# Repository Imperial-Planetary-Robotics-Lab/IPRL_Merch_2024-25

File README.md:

# IPRL_Merch_2024-25
 All the files for the merch

IPRL Rulers:\
[2024 Edition](https://github.com/Imperial-Planetary-Robotics-Lab/IPRL_Merch_2024-25/tree/main/IPRL_2024_Ruler)

[2025 Edition](https://github.com/Imperial-Planetary-Robotics-Lab/IPRL_Merch_2024-25/tree/main/IPRL_2025_Ruler)

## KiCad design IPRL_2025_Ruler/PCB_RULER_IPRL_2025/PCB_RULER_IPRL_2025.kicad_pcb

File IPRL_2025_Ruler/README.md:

# ICRS PCB Ruler

A 15cm PCB ruler variant designed for IPRL. Forked from [here](https://github.com/ben5049/ICRS-PCB-Ruler) (with consent!) It can be easily adapted/rebranded using the KiCad project in this repository.

Front:

Back:

## KiCad Project
To open this project in KiCad 9.0 clone this repository and open the .kicad_pro file in [Ruler_KiCad](Ruler_KiCad). Next open the PCB editor and go to `Preferences > Manage Footprint Libraries > Add Existing` (the folder icon below the list of libraries). Then navigate to `Ruler_KiCad/ruler_footprints` and click "select folder". This is in order to get the custom footprints used in this project.

## Ordering
### PCB
The gerber files needed for ordering can be found in [Ruler_gerbers.zip](https://github.com/Imperial-Planetary-Robotics-Lab/IPRL_Merch_2024-25/blob/main/IPRL_2025_Ruler/PCB_RULER_IPRL_2025/PCB_RULER_IPRL_2025_GERBER.zip). Simply upload this .zip file to any PCB manufacturer's website.

The recommended specifications for ordering this PCB are as follows:
* 2 Layers
* 1.6mm thick FR4
* White silkscreen
* ENIG surface finish
* <= 1 oz Copper weight
* Tented vias
* +- 0.2mm Board outline tolerance
* Remove order number

### Stencils

The stencils are also recommended to order, make sure that customised size is chosen of 160x30. Everything else should be the default values.

## BoM

For the rest of the components on the ruler, here's the bill of materials, that can be bought in bulk in aliExpress

| Reference  | Qty | Value                         | Datasheet                                                                       |
|------------|-----|-------------------------------|---------------------------------------------------------------------------------|
| C101       | 1   | 470p 0402 Capacitor           | ~                                                                               |
| C102       | 1   | 220n 0402 Capacitor           | ~                                                                               |
| C103       | 1   | 1u 0402 Capacitor             | ~                                                                               |
| D101-D112  | 12  | 0402 SMD LED                  | ~                                                                               |
| IC101      | 1   | NT3H2211W0FTTJ                | http://www.nxp.com/docs/en/data-sheet/NT3H2111_2211.pdf                         |
| J101       | 1   | USB_C_Receptacle_PowerOnly_6P | https://www.usb.org/sites/default/files/documents/usb_type-c.zip                |
| R102       | 1   | 47k 0402 Resistor             | ~                                                                               |
| R101, R103 | 1   | 470  0402 Resistor            | ~                                                                               |
| R104,R105  | 2   | 1k  0402 Resistor             | ~                                                                               |
| U101       | 1   | NE555D Clock                  | http://www.ti.com/lit/ds/symlink/ne555.pdf                                      |
| U102       | 1   | 4017 Decade Counter           | http://www.intersil.com/content/dam/Intersil/documents/cd40/cd4017bms-22bms.pdf |

## Assembly and Setup

For the assembly and setup, here's the step-by-step instruction

1. Put solder paste using the stencil, make sure it's cleaned with IPA to avoid putting the paste somewhere else!
2. Put components on top, ensuring correct polarity for the LEDs and ICs (there's usually a dot or a marker to show that)
3. Make sure there's no short, you can start testing it by plugging in the USB-C. The LED under the usb shows power input. If there's no problem, then the LED should start flicking through the symbols.
4. For the NFC, it's a little bit more complicated. First, one person needs to install the NXP tagwriter app.
5. Select Erase tags -> Erase & format as NDEF -> input 2000 bytes -> scan with phone. If you don't know where the NFC on the phone is, the LED on the NFC IC will light up if you're at the right place.
6. Now you should be able to program it with the NFC tools to your heart's content.

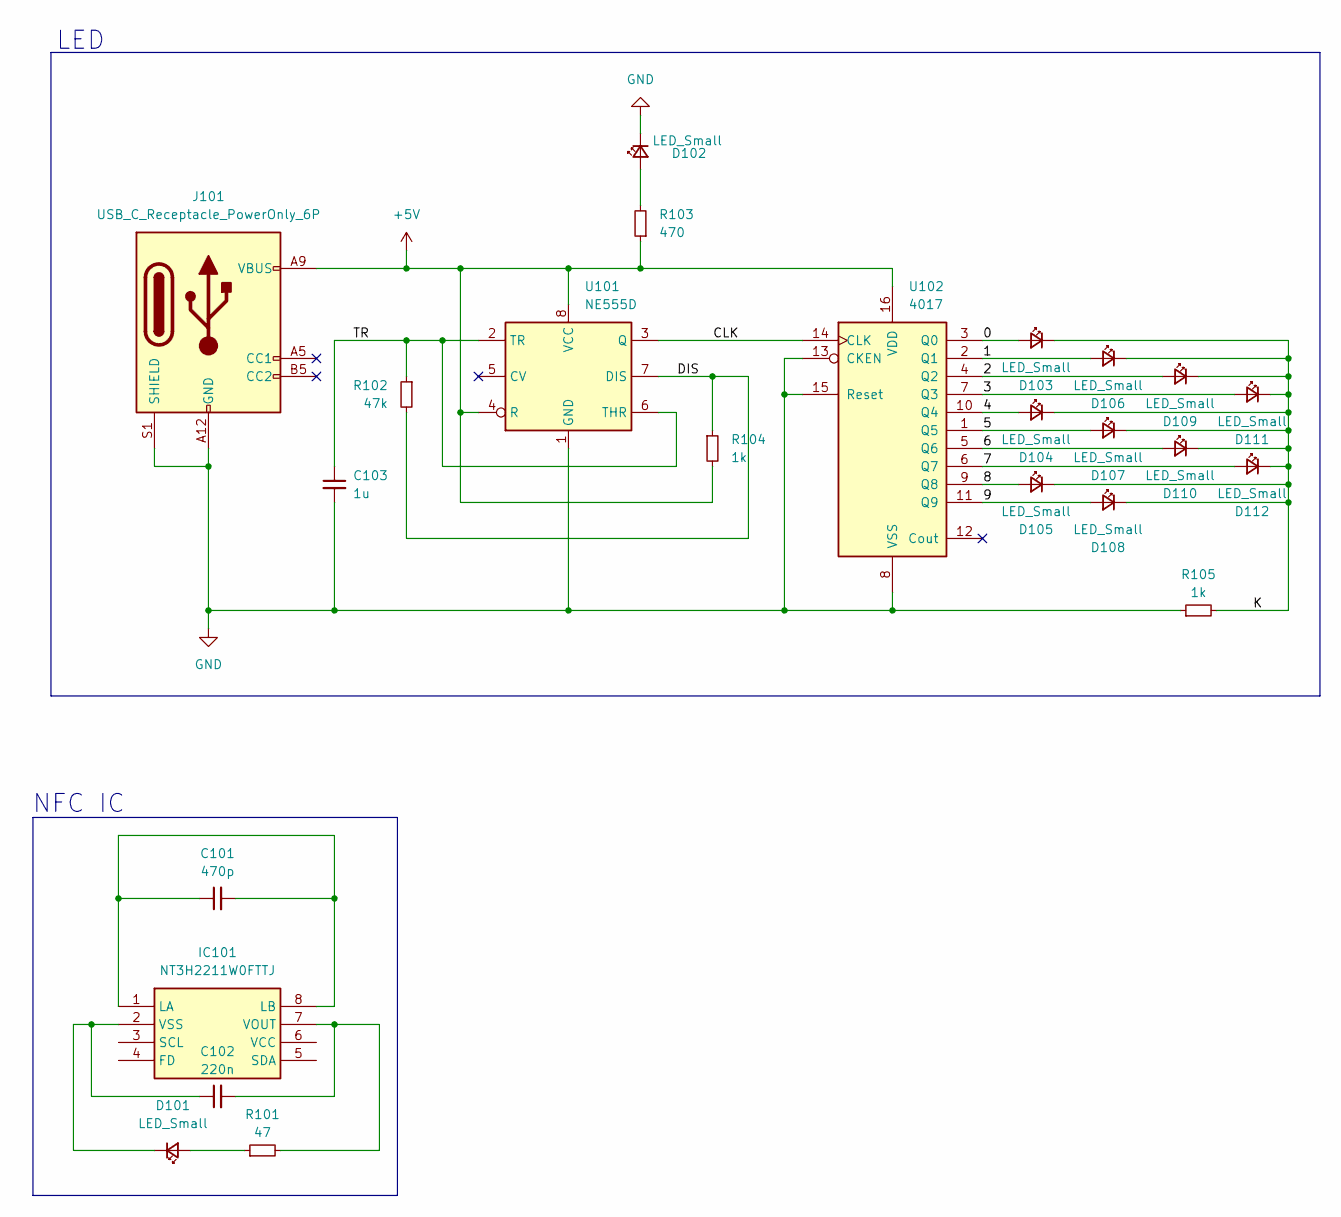
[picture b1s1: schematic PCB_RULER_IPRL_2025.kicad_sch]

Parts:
C101: 470p; C_0402_1005Metric
C102: 220n; C_0402_1005Metric
C103: 1u; C_0402_1005Metric
D101, D102, D103, D104, D105, D106, D107, D108, D109, D110, D111, D112: LED_Small; LED_0402_1005Metric
IC101: NT3H2211W0FTTJ; SOP65P490X110-8N; Mouser Part Number 771-NT3H2211W0FTTJ
J101: USB_C_Receptacle_PowerOnly_6P; USB_C_Receptacle_GCT_USB4135-GF-A_6P_TopMnt_Horizontal
R101: 47; R_0402_1005Metric
R102: 47k; R_0402_1005Metric
R103: 470; R_0402_1005Metric
R104, R105: 1k; R_0402_1005Metric
U101: NE555D; SOIC-8_3.9x4.9mm_P1.27mm
U102: 4017; SOP-16_3.9x9.9mm_P1.27mm

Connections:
+5V: J101.A9 (VBUS), J101.B9 (VBUS), R103.1, R104.2, U101.4 (R), U101.8 (VCC), U102.16 (VDD)
/0: D103.2 (A), U102.3 (Q0)
/1: D106.2 (A), U102.2 (Q1)
/2: D109.2 (A), U102.4 (Q2)
/3: D111.2 (A), U102.7 (Q3)
/4: D104.2 (A), U102.10 (Q4)
/5: D107.2 (A), U102.1 (Q5)
/6: D110.2 (A), U102.5 (Q6)
/7: D112.2 (A), U102.6 (Q7)
/8: D105.2 (A), U102.9 (Q8)
/9: D108.2 (A), U102.11 (Q9)
/CLK: U101.3 (Q), U102.14 (CLK)
/DIS: R102.2, R104.1, U101.7 (DIS)
/K: D103.1 (K), D104.1 (K), D105.1 (K), D106.1 (K), D107.1 (K), D108.1 (K), D109.1 (K), D110.1 (K), D111.1 (K), D112.1 (K), R105.2
/TR: C103.1, R102.1, U101.2 (TR), U101.6 (THR)
GND: C103.2, D102.1 (K), J101.A12 (GND), J101.B12 (GND), J101.S1 (SHIELD), R105.1, U101.1 (GND), U102.8 (VSS), U102.13 (CKEN), U102.15 (Reset)
unnamed: D101.2 (A), R101.1
unnamed: C102.1, D101.1 (K), IC101.2 (VSS)
unnamed: D102.2 (A), R103.2
unnamed: C101.1, C101.2, IC101.1 (LA), IC101.8 (LB)
unnamed: C102.2, IC101.7 (VOUT), R101.2

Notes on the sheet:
LED
NFC IC

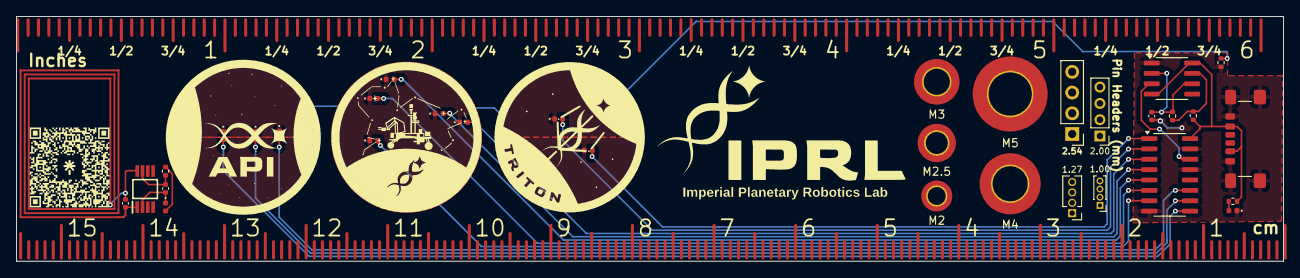
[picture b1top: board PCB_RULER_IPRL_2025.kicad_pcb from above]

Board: 2 copper layers, 155.3 x 30.0 mm, 25 parts (0 on the bottom side), 21 nets.

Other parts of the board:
M2: MountingHole_2.2mm_M2_DIN965_Pad_TopBottom

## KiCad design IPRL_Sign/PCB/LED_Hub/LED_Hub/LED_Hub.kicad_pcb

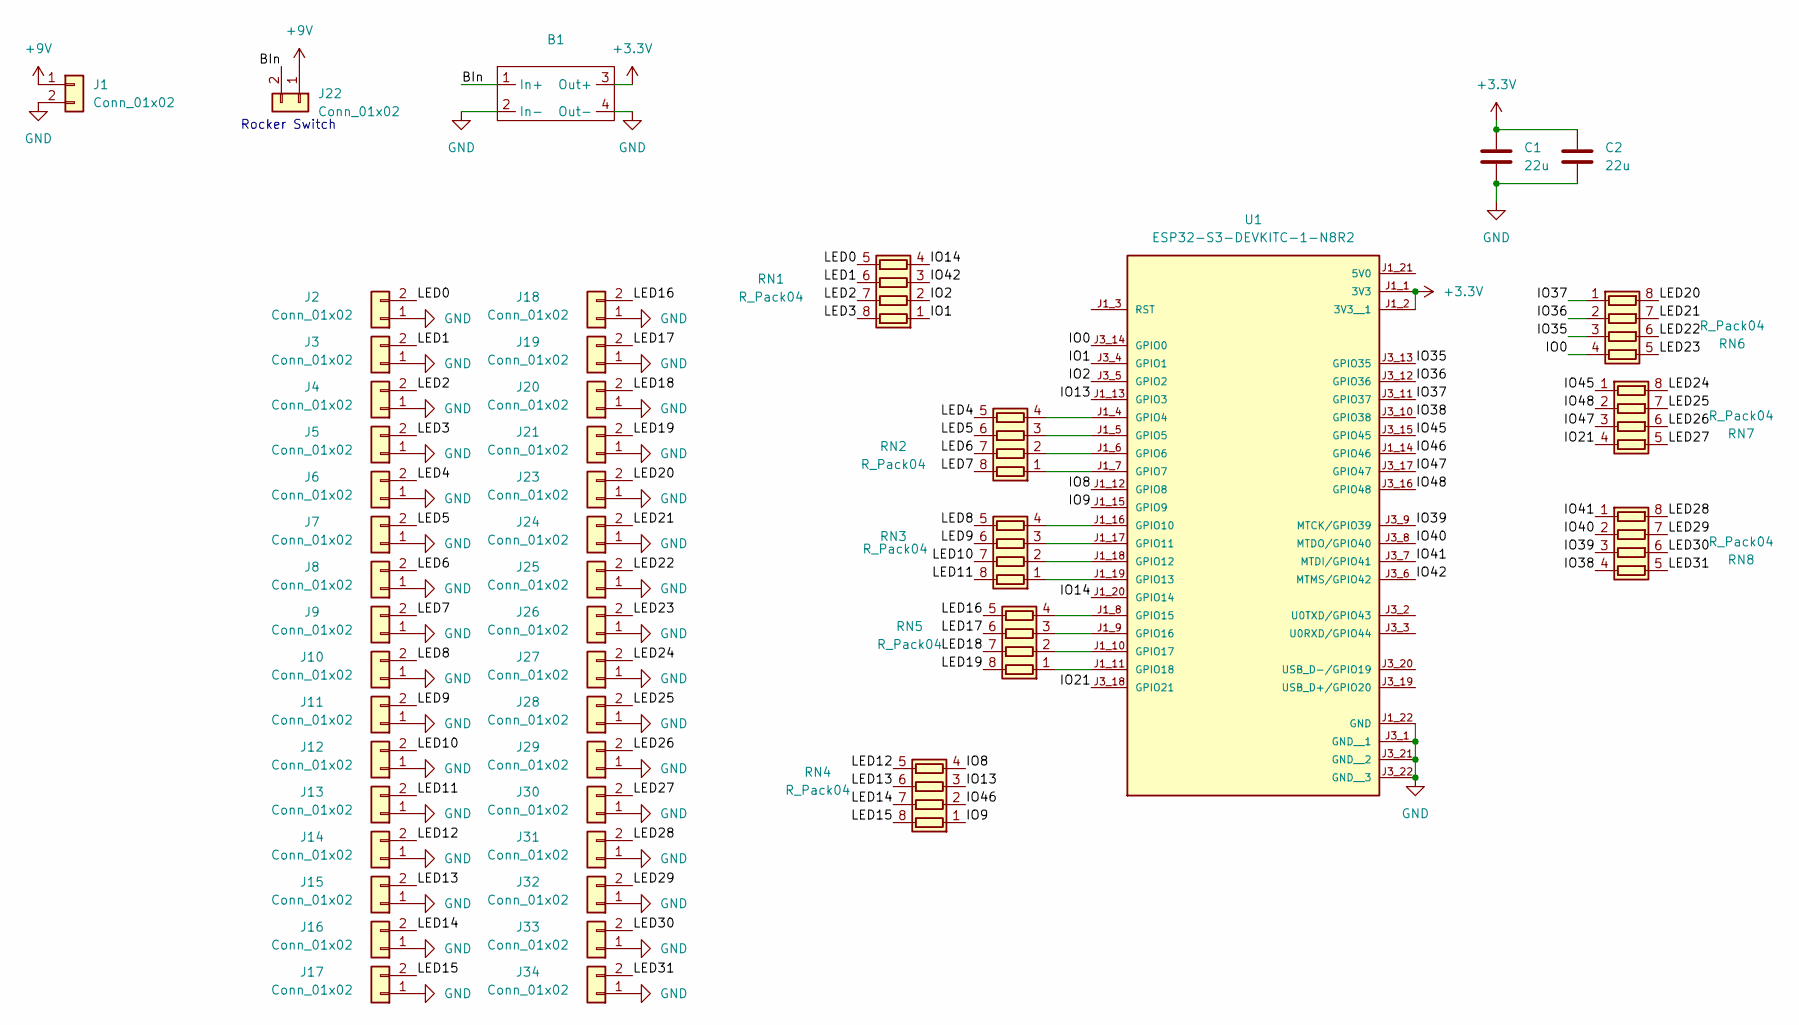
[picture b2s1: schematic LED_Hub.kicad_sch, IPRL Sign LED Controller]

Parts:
B1: MiniBuck
C1: 22u; D_1206_3216Metric
C2: 22u; C_1206_3216Metric
J1, J22: Conn_01x02; JST_XH_B2B-XH-AM_1x02_P2.50mm_Vertical
J2, J3, J4, J5, J6, J7, J8, J9, J10, J11, J12, J13, J14, J15, J16, J17, J18, J19, J20, J21, J23, J24, J25, J26, J27, J28, J29, J30, J31, J32, J33, J34: Conn_01x02; TerminalBlock_MaiXu_MX126-5.0-02P_1x02_P5.00mm
RN1, RN2, RN3, RN4, RN5, RN6, RN7, RN8: R_Pack04; R_Array_Convex_4x0603
U1: ESP32-S3-DEVKITC-1-N8R2; XCVR_ESP32-S3-DEVKITC-1-N8R2; PARTREV V1

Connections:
+3.3V: B1.3 (Out+), C1.1, C2.1, U1.J1_1 (3V3), U1.J1_2 (3V3__1)
+9V: J1.1, J22.1
/BIn: B1.1 (In+), J22.2
/IO0: RN6.4 (R4.1), U1.J3_14 (GPIO0)
/IO1: RN1.1 (R1.1), U1.J3_4 (GPIO1)
/IO2: RN1.2 (R2.1), U1.J3_5 (GPIO2)
/IO8: RN4.4 (R4.1), U1.J1_12 (GPIO8)
/IO9: RN4.1 (R1.1), U1.J1_15 (GPIO9)
/IO13: RN4.3 (R3.1), U1.J1_13 (GPIO3)
/IO14: RN1.4 (R4.1), U1.J1_20 (GPIO14)
/IO21: RN7.4 (R4.1), U1.J3_18 (GPIO21)
/IO35: RN6.3 (R3.1), U1.J3_13 (GPIO35)
/IO36: RN6.2 (R2.1), U1.J3_12 (GPIO36)
/IO37: RN6.1 (R1.1), U1.J3_11 (GPIO37)
/IO38: RN8.4 (R4.1), U1.J3_10 (GPIO38)
/IO39: RN8.3 (R3.1), U1.J3_9 (MTCK/GPIO39)
/IO40: RN8.2 (R2.1), U1.J3_8 (MTDO/GPIO40)
/IO41: RN8.1 (R1.1), U1.J3_7 (MTDI/GPIO41)
/IO42: RN1.3 (R3.1), U1.J3_6 (MTMS/GPIO42)
/IO45: RN7.1 (R1.1), U1.J3_15 (GPIO45)
/IO46: RN4.2 (R2.1), U1.J1_14 (GPIO46)
/IO47: RN7.3 (R3.1), U1.J3_17 (GPIO47)
/IO48: RN7.2 (R2.1), U1.J3_16 (GPIO48)
/LED0: J2.2, RN1.5 (R4.2)
/LED1: J3.2, RN1.6 (R3.2)
/LED2: J4.2, RN1.7 (R2.2)
/LED3: J5.2, RN1.8 (R1.2)
/LED4: J6.2, RN2.5 (R4.2)
/LED5: J7.2, RN2.6 (R3.2)
/LED6: J8.2, RN2.7 (R2.2)
/LED7: J9.2, RN2.8 (R1.2)
/LED8: J10.2, RN3.5 (R4.2)
/LED9: J11.2, RN3.6 (R3.2)
/LED10: J12.2, RN3.7 (R2.2)
/LED11: J13.2, RN3.8 (R1.2)
/LED12: J14.2, RN4.5 (R4.2)
/LED13: J15.2, RN4.6 (R3.2)
/LED14: J16.2, RN4.7 (R2.2)
/LED15: J17.2, RN4.8 (R1.2)
/LED16: J18.2, RN5.5 (R4.2)
/LED17: J19.2, RN5.6 (R3.2)
/LED18: J20.2, RN5.7 (R2.2)
/LED19: J21.2, RN5.8 (R1.2)
/LED20: J23.2, RN6.8 (R1.2)
/LED21: J24.2, RN6.7 (R2.2)
/LED22: J25.2, RN6.6 (R3.2)
/LED23: J26.2, RN6.5 (R4.2)
/LED24: J27.2, RN7.8 (R1.2)
/LED25: J28.2, RN7.7 (R2.2)
/LED26: J29.2, RN7.6 (R3.2)
/LED27: J30.2, RN7.5 (R4.2)
/LED28: J31.2, RN8.8 (R1.2)
/LED29: J32.2, RN8.7 (R2.2)
/LED30: J33.2, RN8.6 (R3.2)
/LED31: J34.2, RN8.5 (R4.2)
GND: B1.2 (In-), B1.4 (Out-), C1.2, C2.2, J1.2, J2.1, J3.1, J4.1, J5.1, J6.1, J7.1, J8.1, J9.1, J10.1, J11.1, J12.1, J13.1, J14.1, J15.1, J16.1, J17.1, J18.1, J19.1, J20.1, J21.1, J23.1, J24.1, J25.1, J26.1, J27.1, J28.1, J29.1, J30.1, J31.1, J32.1, J33.1, J34.1, U1.J1_22 (GND), U1.J3_1 (GND__1), U1.J3_21 (GND__2), U1.J3_22 (GND__3)
unnamed: RN2.1 (R1.1), U1.J1_7 (GPIO7)
unnamed: RN2.2 (R2.1), U1.J1_6 (GPIO6)
unnamed: RN2.3 (R3.1), U1.J1_5 (GPIO5)
unnamed: RN2.4 (R4.1), U1.J1_4 (GPIO4)
unnamed: RN3.1 (R1.1), U1.J1_19 (GPIO13)
unnamed: RN3.2 (R2.1), U1.J1_18 (GPIO12)
unnamed: RN3.3 (R3.1), U1.J1_17 (GPIO11)
unnamed: RN3.4 (R4.1), U1.J1_16 (GPIO10)
unnamed: RN5.1 (R1.1), U1.J1_11 (GPIO18)
unnamed: RN5.2 (R2.1), U1.J1_10 (GPIO17)
unnamed: RN5.3 (R3.1), U1.J1_9 (GPIO16)
unnamed: RN5.4 (R4.1), U1.J1_8 (GPIO15)

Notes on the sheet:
Rocker Switch

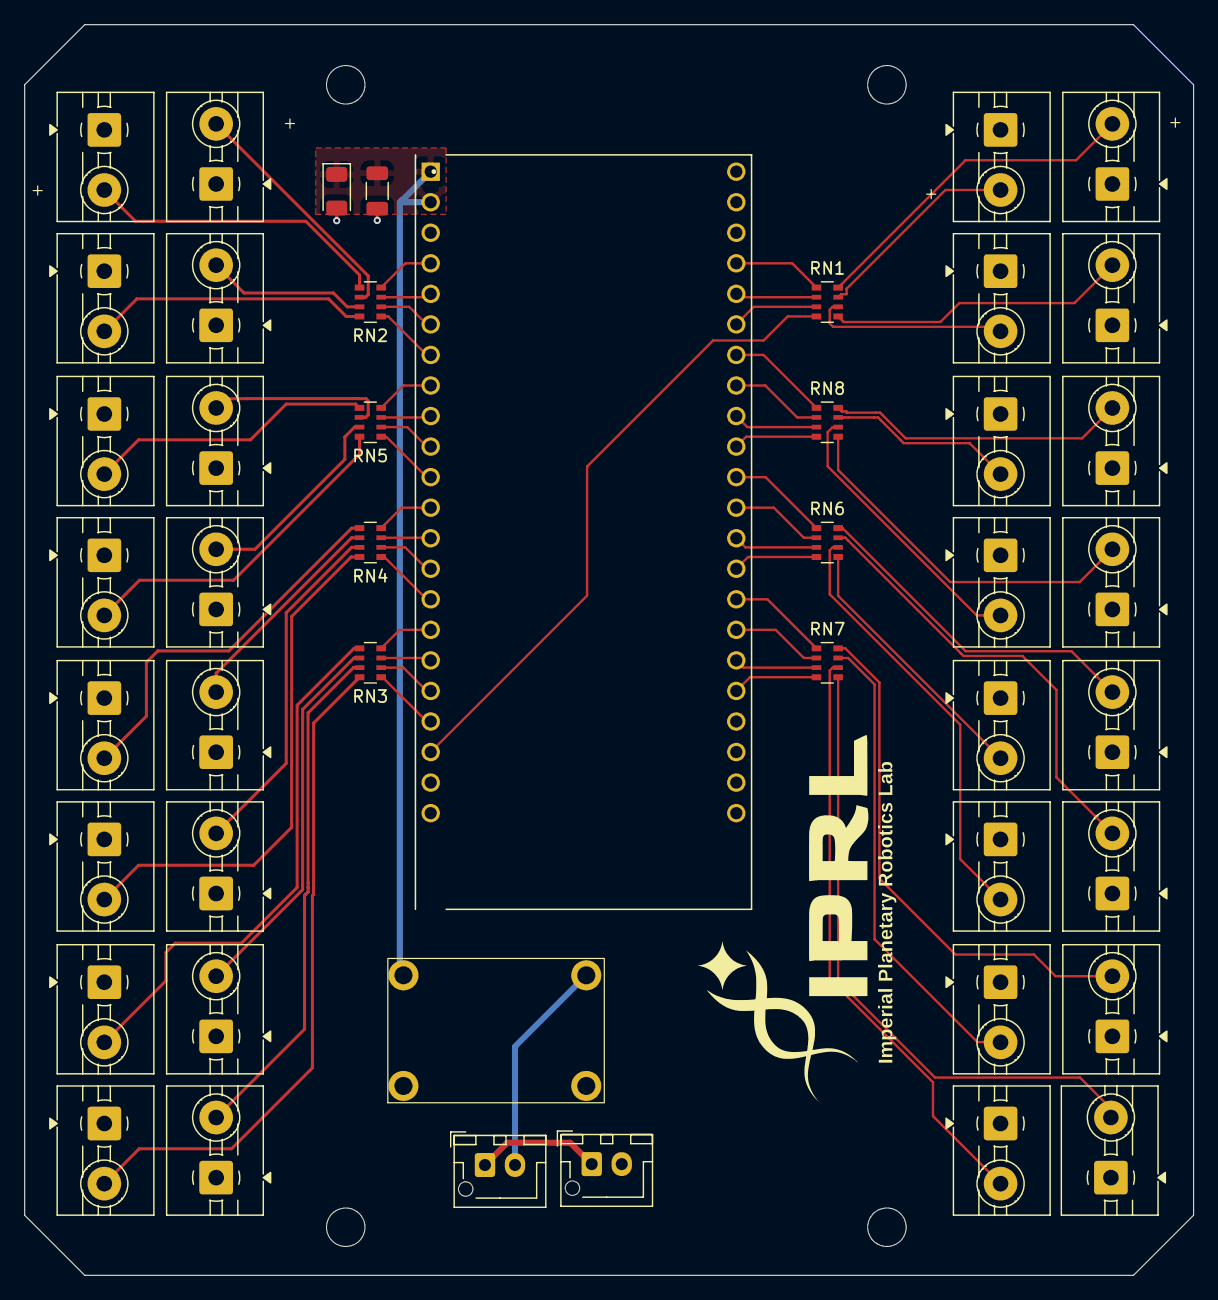
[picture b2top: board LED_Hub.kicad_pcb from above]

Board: 2 copper layers, 97.2 x 104.0 mm, 46 parts (0 on the bottom side), 68 nets.

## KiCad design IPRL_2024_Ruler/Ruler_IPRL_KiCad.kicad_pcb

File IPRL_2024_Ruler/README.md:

# ICRS PCB Ruler

A 15cm PCB ruler variant designed for IPRL. Taken straight from [here](https://github.com/ben5049/ICRS-PCB-Ruler) (with consent!) It can be easily adapted/rebranded using the KiCad project in this repository.

Front:

Back:

## KiCad Project
To open this project in KiCad 8.0 clone this repository and open the .kicad_pro file in [Ruler_KiCad](Ruler_KiCad). Next open the PCB editor and go to `Preferences > Manage Footprint Libraries > Add Existing` (the folder icon below the list of libraries). Then navigate to `Ruler_KiCad/ruler_footprints` and click "select folder". This is in order to get the custom footprints used in this project.

## Ordering
The gerber files needed for ordering can be found in [Ruler_gerbers.zip](Ruler_KiCad/Ruler_gerbers/Ruler_gerbers.zip). Simply upload this .zip file to any PCB manufacturer's website.

The recommended specifications for ordering this PCB are as follows:
* 2 Layers
* 1.6mm thick FR4
* Blue soldermask
* White silkscreen
* ENIG surface finish
* <= 1 oz Copper weight
* Tented vias (doesn't matter as there are no vias)
* +- 0.2mm Board outline tolerance
* Remove order number

Using [JLCPCB's](https://jlcpcb.com/) pricing, the cost of ordering x number of boards has been plotted in [Pricing.xlsx](Pricing.xlsx).

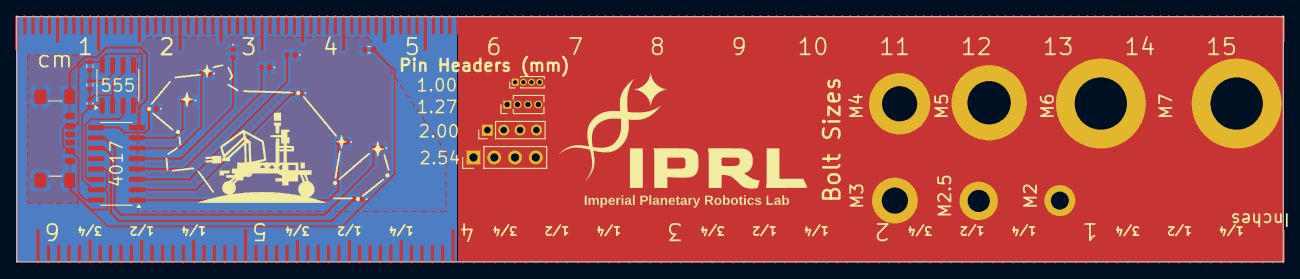
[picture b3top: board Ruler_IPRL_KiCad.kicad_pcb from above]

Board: 2 copper layers, 155.0 x 30.0 mm, 17 parts (0 on the bottom side), 16 nets.

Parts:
C101: 1u; C_0402_1005Metric
D101, D102, D103, D104, D105, D106, D107, D108, D109, D110: LED_Small; LED_0402_1005Metric
J102: USB_C_Receptacle_PowerOnly_6P; USB_C_Receptacle_GCT_USB4135-GF-A_6P_TopMnt_Horizontal
R101, R102: 1k; R_0402_1005Metric
R103: 47k; R_0402_1005Metric
U101: NE555D; SOIC-8_3.9x4.9mm_P1.27mm
U102: 4017; SOP-16_3.9x9.9mm_P1.27mm

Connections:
+5V: J102.A9 (VBUS), J102.B9 (VBUS), R101.2, U101.4 (R), U101.8 (VCC), U102.16 (VDD)
/0: D109.2 (A), U102.3 (Q0)
/1: D104.2 (A), U102.2 (Q1)
/2: D103.2 (A), U102.4 (Q2)
/3: D106.2 (A), U102.7 (Q3)
/4: D101.2 (A), U102.10 (Q4)
/5: D110.2 (A), U102.1 (Q5)
/6: D105.2 (A), U102.5 (Q6)
/7: D107.2 (A), U102.6 (Q7)
/8: D108.2 (A), U102.9 (Q8)
/9: D102.2 (A), U102.11 (Q9)
/CLK: U101.3 (Q), U102.14 (CLK)
/DIS: R101.1, R103.2, U101.7 (DIS)
/K: D101.1 (K), D102.1 (K), D103.1 (K), D104.1 (K), D105.1 (K), D106.1 (K), D107.1 (K), D108.1 (K), D109.1 (K), D110.1 (K), R102.2
/TR: C101.1, R103.1, U101.2 (TR), U101.6 (THR)
GND: C101.2, J102.A12 (GND), J102.B12 (GND), J102.S1 (SHIELD), R102.1, U101.1 (GND), U102.8 (VSS), U102.13 (CKEN), U102.15 (Reset)

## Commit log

2024-09-12 Added IPRL Ruler
2025-03-29 Added 2025 folder
2025-04-02 Added NFC capabilities
2025-04-21 Added LED Connector + LED_Hub
2025-04-21 Added pdfs
2025-07-21 Front side IPRL 2025 Ruler
2025-07-24 Added member names
2025-08-19 IPRL2025Ruler completed
2025-09-04 Finalised IPRL PCB pre-colour
2025-09-05 Completed IPRL Ruler 2025
2025-09-05 Updated Main README
2025-09-05 Front Readme fix
2025-09-05 Image Fix
2025-09-05 Added 2025 README
2025-09-05 IPRL_2025_README
2025-09-05 Minor README Edits
2025-09-05 Changed Position of silkscreen
2025-09-05 autosave
